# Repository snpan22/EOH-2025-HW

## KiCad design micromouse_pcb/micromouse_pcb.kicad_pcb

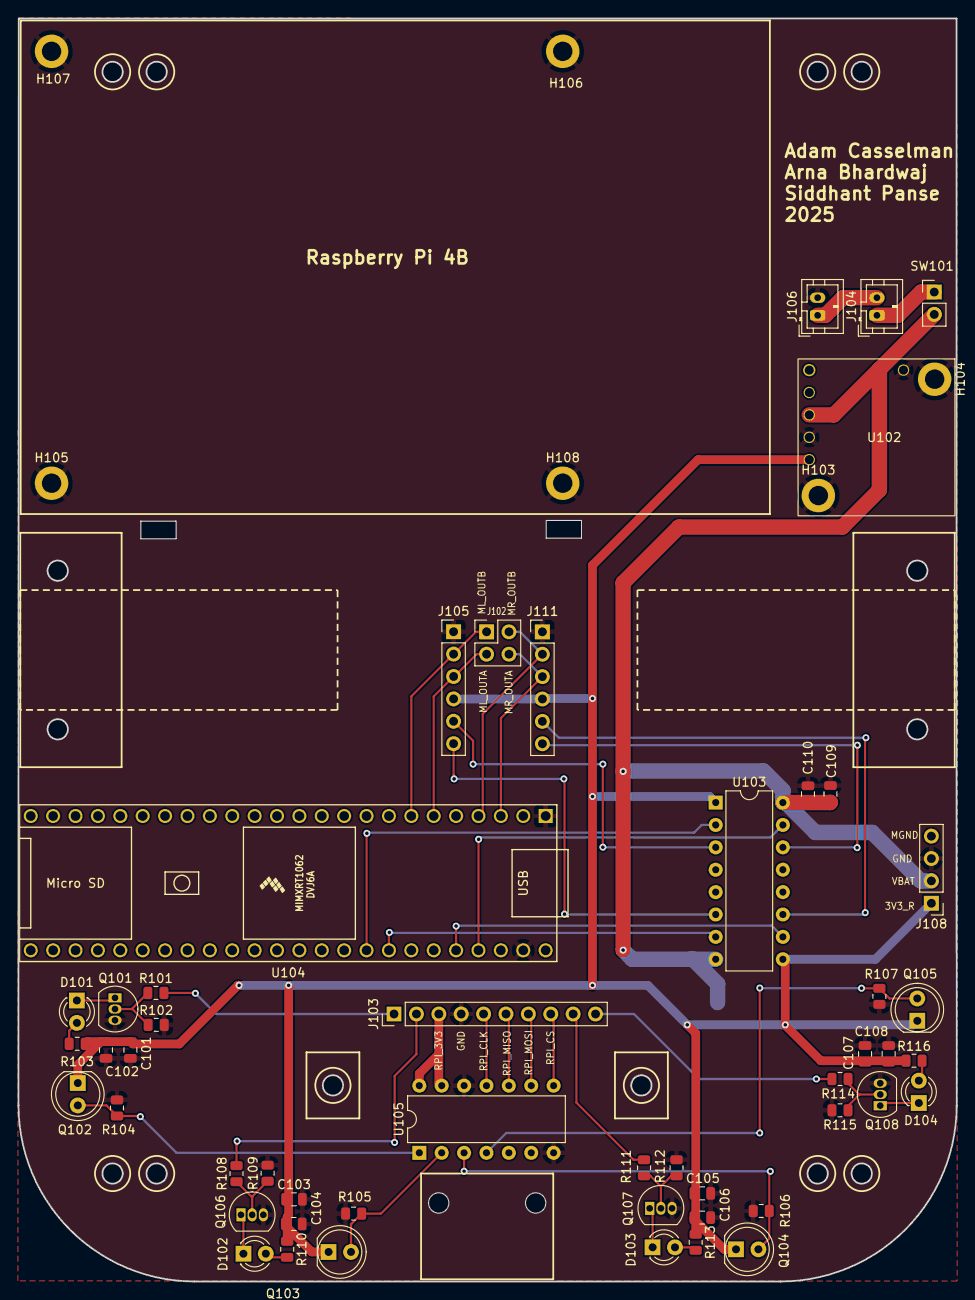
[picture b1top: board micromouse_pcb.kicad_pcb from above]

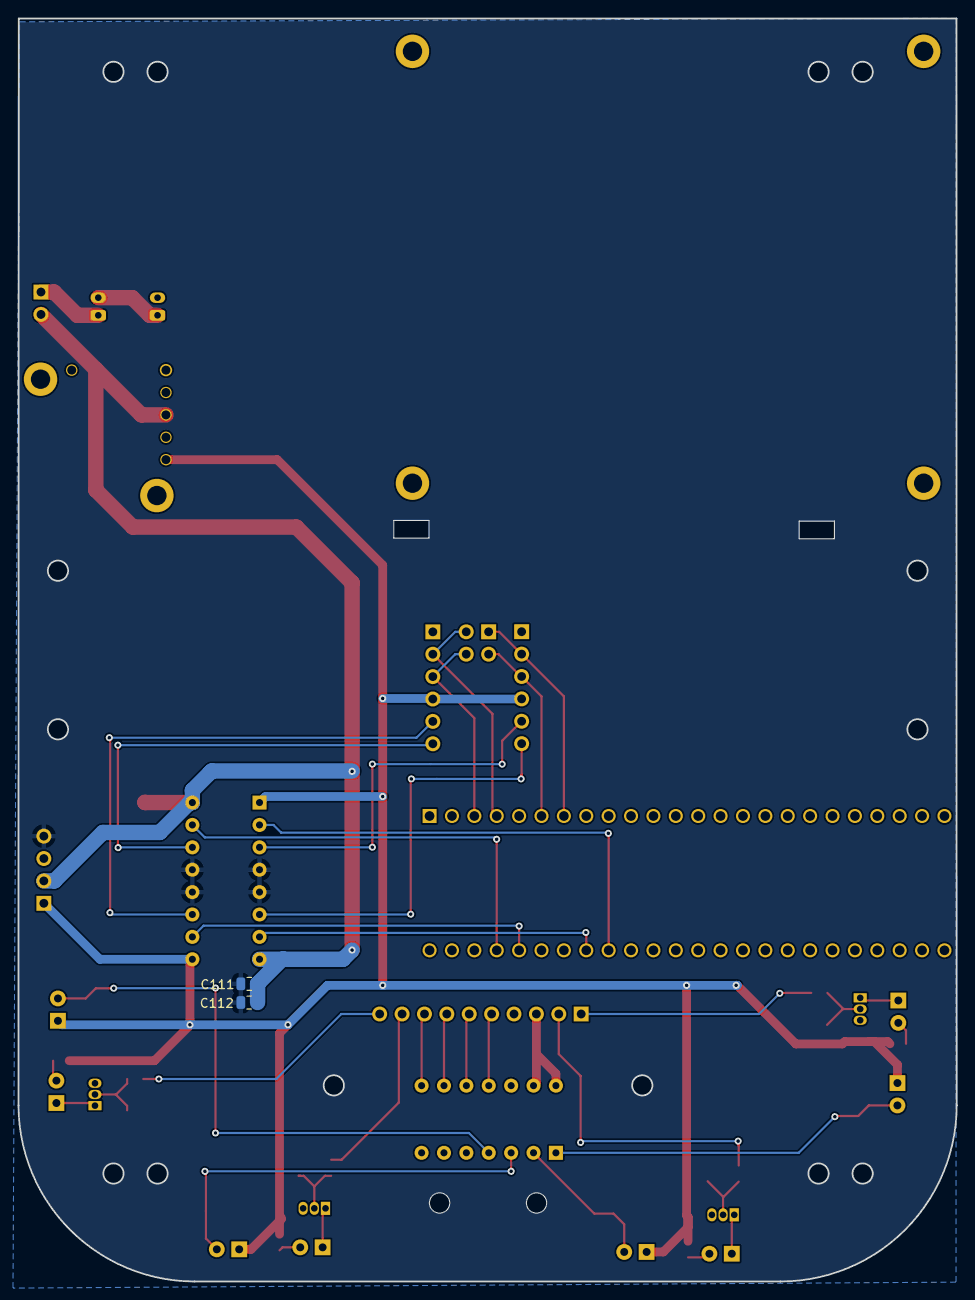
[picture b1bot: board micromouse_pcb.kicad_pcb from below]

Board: 2 copper layers, 106.5 x 143.3 mm, 58 parts (2 on the bottom side), 43 nets.

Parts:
C101, C103, C105, C107: 4.7 uF; C_0805_2012Metric
C102, C104, C106, C108, C109: 0.1 uF; C_0805_2012Metric
C110, C111: 4.7uF; C_0805_2012Metric
C112: 10uF; C_0805_2012Metric
D101, D102, D103, D104: INL-5AMIR15; LED_D3.0mm_IRBlack
H103, H104, H105, H106, H107, H108: MountingHole_Pad; MountingHole_2.2mm_M2_DIN965_Pad
J102: Conn_02x02_Counter_Clockwise; PinHeader_2x02_P2.54mm_Vertical
J103: Conn_01x10; PinHeader_1x10_P2.54mm_Vertical
J104, J106: Conn_01x02; JST_PH_B2B-PH-K_1x02_P2.00mm_Vertical
J105, J111: Conn_01x06; PinHeader_1x06_P2.54mm_Vertical
J108: Conn_01x04; PinHeader_1x04_P2.54mm_Vertical
Q101, Q106, Q107, Q108: BS170; TO-92_Inline
Q102, Q103, Q104, Q105: SFH313FA; LED_D5.0mm_Clear
R101, R108, R111, R114: 100; R_0805_2012Metric
R102, R109, R112, R115: 47K; R_0805_2012Metric
R103: 51Ohm; R_0805_2012Metric
R104, R105, R106, R107: 1.8k; R_0805_2012Metric
R110, R113: 51 Ohm; R_0805_2012Metric
R116: 50 Ohm; R_0805_2012Metric
SW101: SW_SPST; PinHeader_1x02_P2.54mm_Vertical
U102: D24V22FX
U103: L293D; DIP-16_W7.62mm
U104: Teensy4.1_bare; Teensy41_bare_pins
U105: MCP3004; DIP-14_W7.62mm

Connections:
/3V3_REGULATED: C101.1, C102.1, C103.1, C104.1, C105.1, C106.1, C107.1, C108.1, J105.4, J108.1, J111.4, Q102.1 (C), Q103.1 (C), Q104.1 (C), Q105.1 (C), R103.1, R110.1, R113.1, R116.1, U102.5 (VOUT), U103.1 (EN1,2), U103.9 (EN3,4)
/IR_EMITTER_1: J103.1, R101.2
/IR_EMITTER_2: J103.2, R108.2
/IR_EMITTER_3: J103.9, R111.2
/IR_EMITTER_4: J103.10, R114.2
/IR_RECEIVER_1: Q102.2 (E), R104.1, U105.1 (CH0)
/IR_RECEIVER_2: Q103.2 (E), R105.1, U105.2 (CH1)
/IR_RECEIVER_3: Q104.2 (E), R106.1, U105.3 (CH2)
/IR_RECEIVER_4: Q105.2 (E), R107.1, U105.4 (CH3)
/MGND: C111.2, C112.1, J108.4, U103.4 (GND), U103.5 (GND), U103.12 (GND), U103.13 (GND)
/ML_1: J105.6, U103.6 (2Y)
/ML_2: J105.5, U103.3 (1Y)
/ML_IN_1: U103.7 (2A), U104.41 (19_A5_SCL)
/ML_IN_2: U103.2 (1A), U104.40 (18_A4_SDA)
/ML_OUTA: J102.3, J105.3, U104.6 (4_BCLK2)
/ML_OUTB: J102.1, J105.2, U104.7 (5_IN2)
/MR_1: J111.6, U103.14 (4Y)
/MR_2: J111.5, U103.11 (3Y)
/MR_IN_1: U103.15 (4A), U104.45 (23_A9_CRX1_MCLK1)
/MR_IN_2: U103.10 (3A), U104.44 (22_A8_CTX1)
/MR_OUTA: J102.4, J111.3, U104.3 (1_TX1_CTX2_MISO1)
/MR_OUTB: J102.2, J111.2, U104.4 (2_OUT2)
/RPI_3V3: J103.3, U105.13 (Vref), U105.14 (Vdd)
/RPI_CLK: J103.5, U105.11 (CLK)
/RPI_CS: J103.8, U105.8 (~CS/SHDN)
/RPI_MISO: J103.6, U105.10 (Dout)
/RPI_MOSI: J103.7, U105.9 (Din)
/VBAT: C109.2, C110.2, C111.1, C112.2, J108.2, SW101.2 (B), U102.3 (VIN), U103.8 (VCC2), U103.16 (VCC1)
GND: C101.2, C102.2, C103.2, C104.2, C105.2, C106.2, C107.2, C108.2, C109.1, C110.1, H103.1, H104.1, H105.1, H106.1, H107.1, H108.1, J103.4, J105.1, J106.2, J108.3, J111.1, Q101.3 (S), Q106.3 (S), Q107.3 (S), Q108.3 (S), R102.2, R104.2, R105.2, R106.2, R107.2, R109.2, R112.2, R115.2, U102.4 (GND), U102.6 (GND), U104.1 (GND), U104.47 (GND), U105.7 (DGND), U105.12 (AGND)
unnamed: D101.2 (A), R103.2
unnamed: D101.1 (K), Q101.1 (D)
unnamed: D102.2 (A), R110.2
unnamed: D102.1 (K), Q106.1 (D)
unnamed: D103.2 (A), R113.2
unnamed: D103.1 (K), Q107.1 (D)
unnamed: D104.2 (A), R116.2
unnamed: D104.1 (K), Q108.1 (D)
unnamed: J104.1, SW101.1 (A)
unnamed: J104.2, J106.1
unnamed: Q101.2 (G), R101.1, R102.1
unnamed: Q106.2 (G), R108.1, R109.1
unnamed: Q107.2 (G), R111.1, R112.1
unnamed: Q108.2 (G), R114.1, R115.1

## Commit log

2024-12-21 added blank schematic and pcb file
2024-12-23 Added teensy, Motor driver connections, and connector for Raspberry Pi GPIO
2024-12-26 added regulators and motor encoders schematic
2024-12-27 general board layout established v1
2024-12-29 last push before new branch
2025-01-01 first iteration of pin assignments and routing done
2025-01-10 cleaned up schematic
2025-01-19 updated pcb
2025-01-22 added mounting holes
